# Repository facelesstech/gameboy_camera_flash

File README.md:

# gameboy_camera_flash
gameboy_camera_flash

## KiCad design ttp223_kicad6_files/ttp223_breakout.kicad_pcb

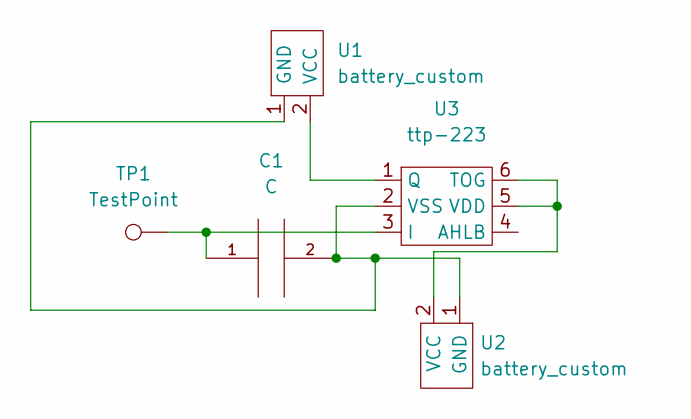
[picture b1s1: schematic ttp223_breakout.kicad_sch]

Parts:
C1: C; C_0603_1608Metric_Pad1.08x0.95mm_HandSolder
TP1: TestPoint; 1mm_test_point
U1, U2: battery_custom; vcc_gnd_2pin_custom_thin
U3: ttp-223; SOT-23-6_Handsoldering

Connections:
unnamed: C1.1, TP1.1, U3.3 (I)
unnamed: C1.2, U1.1 (GND), U2.1 (GND), U3.2 (VSS)
unnamed: U1.2 (VCC), U3.1 (Q)
unnamed: U2.2 (VCC), U3.5 (VDD), U3.6 (TOG)

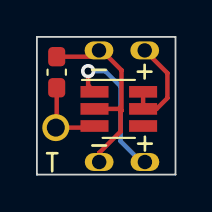
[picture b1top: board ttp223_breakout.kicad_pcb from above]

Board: 2 copper layers, 7.7 x 7.7 mm, 5 parts (0 on the bottom side), 4 nets.

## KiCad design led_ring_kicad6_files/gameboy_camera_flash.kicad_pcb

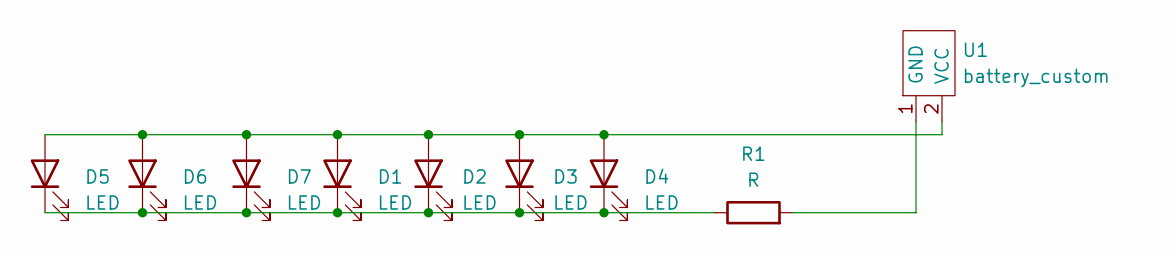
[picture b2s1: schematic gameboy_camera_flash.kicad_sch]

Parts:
D1, D2, D3, D4, D5, D6, D7: LED; LED_0603_1608Metric_Pad1.05x0.95mm_HandSolder
R1: R; R_0603_1608Metric_Pad0.98x0.95mm_HandSolder
U1: battery_custom; vcc_gnd_2pin_custom_smd_close

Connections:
unnamed: D1.1 (K), D2.1 (K), D3.1 (K), D4.1 (K), D5.1 (K), D6.1 (K), D7.1 (K), R1.1
unnamed: D1.2 (A), D2.2 (A), D3.2 (A), D4.2 (A), D5.2 (A), D6.2 (A), D7.2 (A), U1.2 (VCC)
unnamed: R1.2, U1.1 (GND)

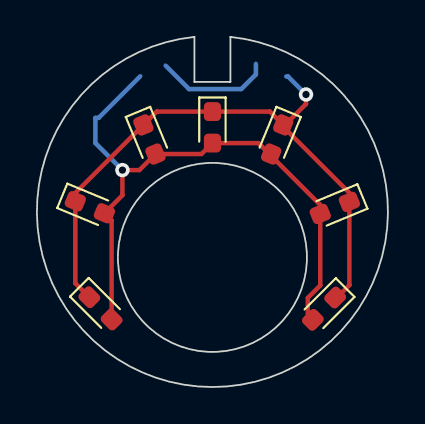
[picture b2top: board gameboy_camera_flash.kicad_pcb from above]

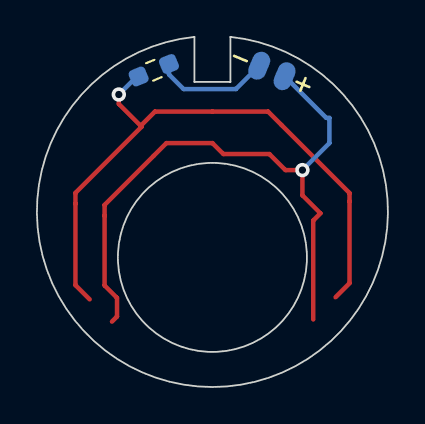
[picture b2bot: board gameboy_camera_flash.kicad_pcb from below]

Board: 2 copper layers, 19.5 x 19.5 mm, 9 parts (2 on the bottom side), 3 nets.

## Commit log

2023-06-11 added led ring files
2023-06-11 added ttp223 files
